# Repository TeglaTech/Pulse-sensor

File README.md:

# Pulse-sensor
Instructions and Eagle files for ELAB's DIY pulse sensor PCB.

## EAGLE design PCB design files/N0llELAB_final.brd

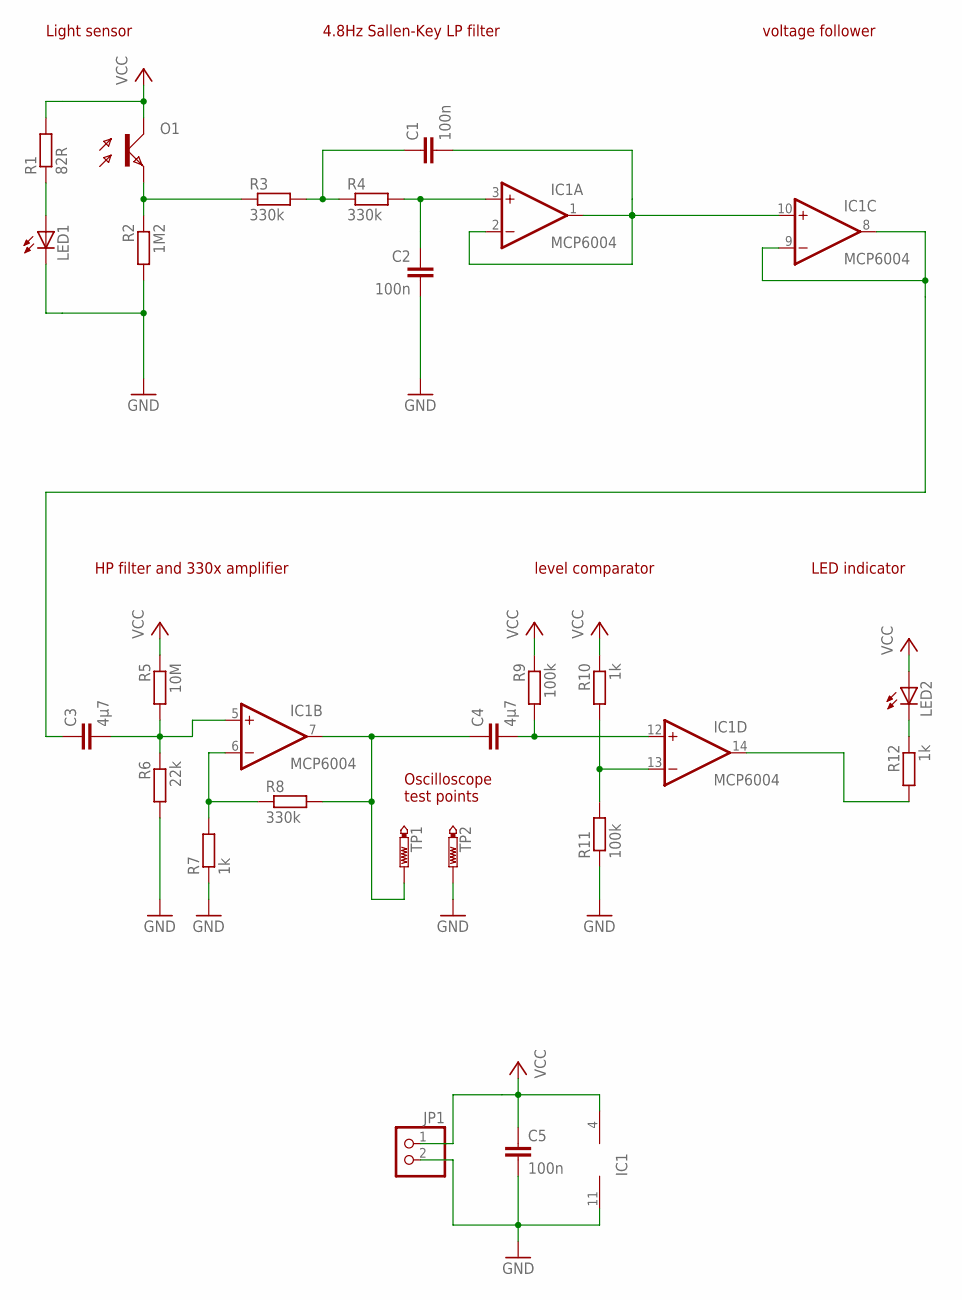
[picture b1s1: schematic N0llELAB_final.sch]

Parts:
C1, C2, C5: 100n; C050-024X044
C3, C4: 4µ7; C050-024X044
IC1: MCP6004; DIL14
JP1: PINHD-1X02_2.54-S; 1X02-S
LED1: LED5MM-90L
LED2: LED5MM
O1: OPTOTRANS5MM-90R; LED5MM-90R
R1: 82R; 0207/2V
R2: 1M2; 0207/2V
R3, R4, R8: 330k; 0207/2V
R5: 10M; 0207/2V
R6: 22k; 0207/2V
R7, R10, R12: 1k; 0207/2V
R9, R11: 100k; 0207/2V
TP1, TP2: PTR1PAD1-13; P1-13

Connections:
GND: C2.2, C5.2, IC1.11 (V-), JP1.2, LED1.K (C), R2.2, R6.2, R7.1, R11.1, TP2.1
unnamed: O1.A (E), R2.1, R3.1
unnamed: C2.1, IC1.3 (+IN), R4.2
unnamed: C1.1, R3.2, R4.1
unnamed: C4.2, IC1.12 (+IN), R9.2
unnamed: IC1.13 (-IN), R10.2, R11.2
unnamed: IC1.14 (OUT), R12.2
unnamed: LED2.K (C), R12.1
unnamed: LED1.A, R1.1
unnamed: C3.1, IC1.8 (OUT), IC1.9 (-IN)
unnamed: C1.2, IC1.1 (OUT), IC1.2 (-IN), IC1.10 (+IN)
unnamed: C3.2, IC1.5 (+IN), R5.2, R6.1
unnamed: IC1.6 (-IN), R7.2, R8.1
unnamed: C4.1, IC1.7 (OUT), R8.2, TP1.1
VCC: C5.1, IC1.4 (V+), JP1.1, LED2.A, O1.K (C), R1.2, R5.1, R9.1, R10.1

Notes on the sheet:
4.8Hz Sallen-Key LP filter
voltage follower
Light sensor
HP filter and 330x amplifier
level comparator
LED indicator
Oscilloscope test points
IC1

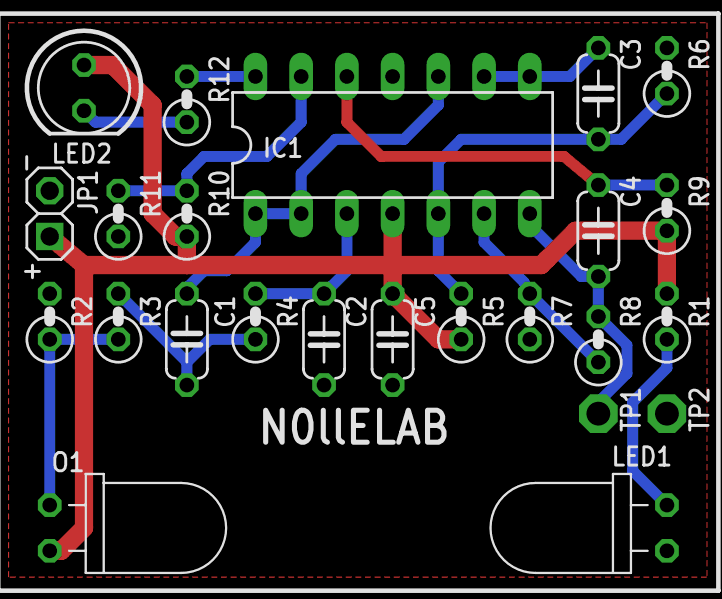
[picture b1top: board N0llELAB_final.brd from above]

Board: 2 copper layers, 24 parts (0 on the bottom side), 15 nets.
